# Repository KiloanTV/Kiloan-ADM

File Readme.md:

<div>
  <h1 align="center">Kiloan ADM V1</h1>

  <p align="center">
  <a href="https://blueprint.hackclub.com/">
    </img>
  </a>
  </p>
  <h1></h1>
  <p align="center">
    A 8-Channel Analog to Digital Converter for my custom digital mixing console!
  </p>
</div>

<sub align="center">This work is licensed under the
[MIT License](https://mit-license.org).
</sub>

## Table of Contents

- [About](#about)
- [Pictures](#pictures)
- [Bill of Materials](#bill-of-materials)

# About

I've always wanted my own digital mixing console, but those things are just too expensive for teenagers. That's why I want to build my own! This is the expansion board for 8 analog inputs, it receives power from the motherboard and outputs digital signals via the expansion connector to the Kiloan-APU board.

# Pictures

# Bill of Materials

<details>
<summary><strong>Show Bill Of Materials(BOM) ----></strong></summary>

|Designator                                                                                                        |Footprint                                  |Quantity|Value                               |LCSC Part #|
|------------------------------------------------------------------------------------------------------------------|-------------------------------------------|--------|------------------------------------|-----------|
|C1, C11, C12, C17, C18, C2, C25, C26, C29, C30, C39, C40, C45, C46, C51, C52, C59, C60, C7, C79, C8, C80, C83, C84|0805                                       |24      |100pF                               |C2167185   |
|C10, C19, C20, C27, C28, C3, C4, C41, C42, C49, C50, C75, C76, C81, C82, C9                                       |0805                                       |16      |220pF                               |C569853    |
|C13, C14, C15, C16, C21, C31, C32, C33, C34, C35, C37, C47, C55, C56, C57, C58, C85, C86, C87, C88                |CP_Radial_D5.0mm_P2.00mm                   |20      |100uF                               |C136287    |
|C22, C36, C38, C48, C53                                                                                           |0805                                       |5       |100nF                               |C3018562   |
|C23, C24, C43, C44, C5, C6, C77, C78                                                                              |0805                                       |8       |1nF                                 |C178423    |
|C54                                                                                                               |0805                                       |1       |4.7uF                               |C162418    |
|C61, C62, C63, C64, C65, C66, C67, C68, C71, C72, C74                                                             |0805                                       |11      |50V 100nF                           |C3018562   |
|C69, C70, C73                                                                                                     |0805                                       |3       |25V 10uF                            |C391262    |
|IC1                                                                                                               |QFN-64-1EP_9x9mm_P0.5mm_EP6x6mm_ThermalVias|1       |8-Channel Differential 32-bit △∑ ADC|C2655448   |
|IC201, IC202, IC203, IC204, IC205, IC206, IC207, IC208                                                            |SOIC-8_3.9x4.9mm_P1.27mm                   |8       |TI OPA1652AIDR                      |           |
|J1                                                                                                                |JST_PH_B4B-PH-K_1x04_P2.00mm_Vertical      |1       |PowerConAD-Wandler                  |C131334    |
|J2                                                                                                                |JST_PH_B8B-PH-K_1x08_P2.00mm_Vertical      |1       |AD-Wandler CON                      |C157974    |
|R1, R15, R16, R17, R18, R2, R32, R33, R36, R37, R52, R53, R54, R55, R68, R69                                      |0805                                       |16      |6800Ω                               |C2092414   |
|R10, R14, R21, R22, R27, R31, R41, R42, R47, R5, R51, R58, R59, R6, R63, R67                                      |0805                                       |16      |10Ω                                 |C2479122   |
|R11, R12, R24, R25, R28, R29, R44, R45, R48, R49, R60, R61, R64, R65, R7, R8                                      |0805                                       |16      |10kΩ                                |C2441435   |
|R13, R19, R20, R26, R3, R30, R39, R4, R40, R46, R50, R56, R57, R62, R66, R9                                       |0805                                       |16      |2200Ω                               |C2085959   |
|R23, R34, R35, R43                                                                                                |0805                                       |4       |20Ω                                 |C114557    |
|R38                                                                                                               |0805                                       |1       |33Ω ±1%                             |C126353    |
|X1                                                                                                                |JST_PHD_B26B-PHDSS_2x13_P2.00mm_Vertical   |1       |IN_CON                              |C3011993   |
| LCSC Quote: 47,54 Dollar + JLCPCP Quote: 27,65 Dollar                                                                                                                |    |        |                              |    |

</details>

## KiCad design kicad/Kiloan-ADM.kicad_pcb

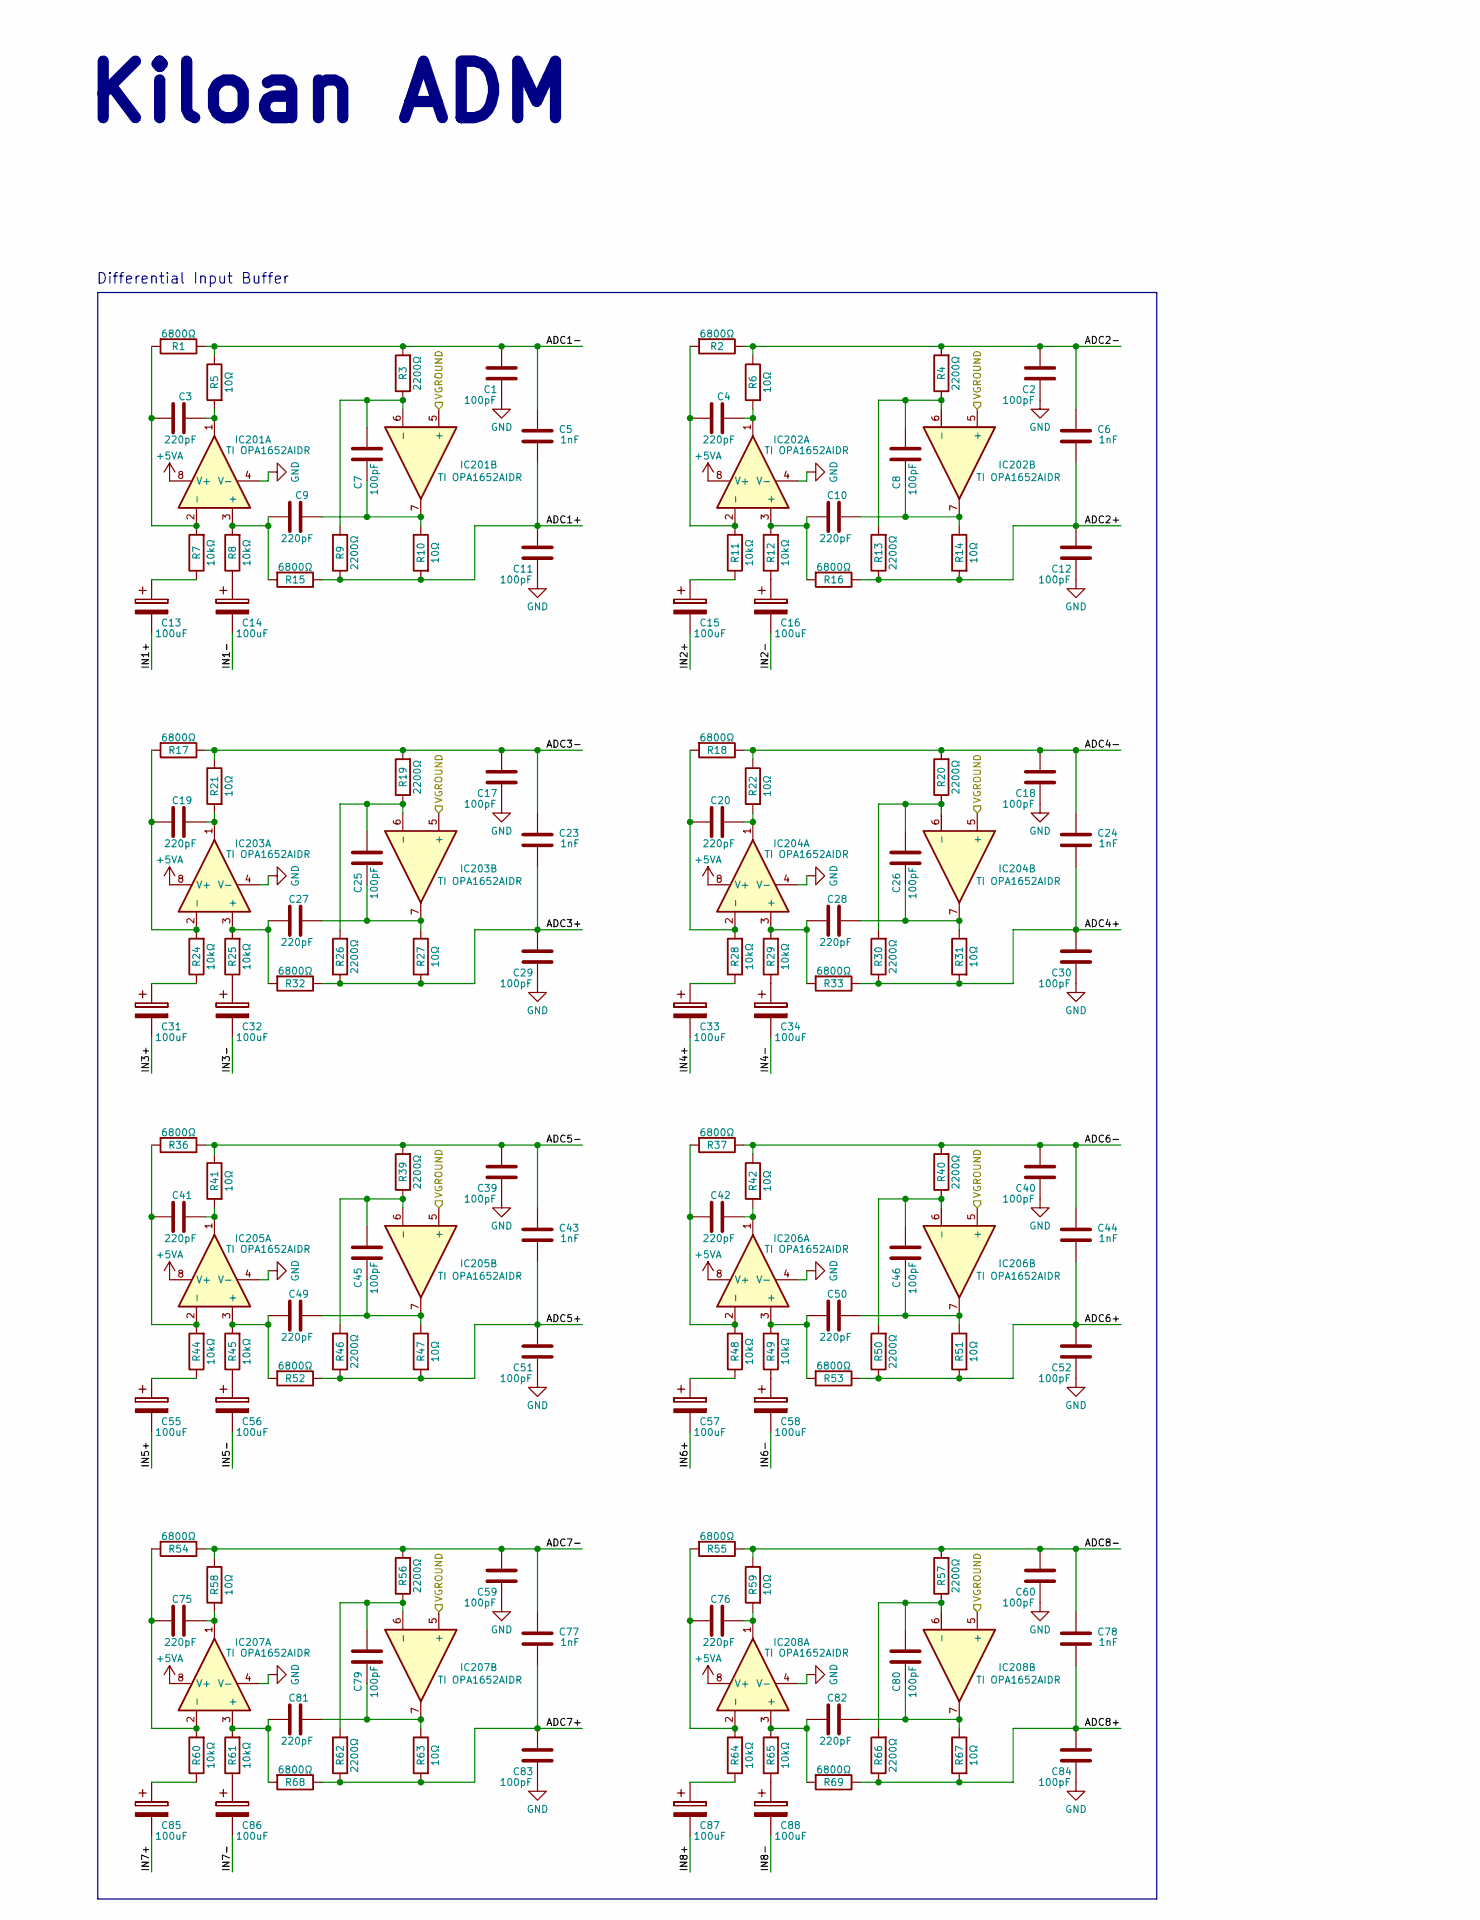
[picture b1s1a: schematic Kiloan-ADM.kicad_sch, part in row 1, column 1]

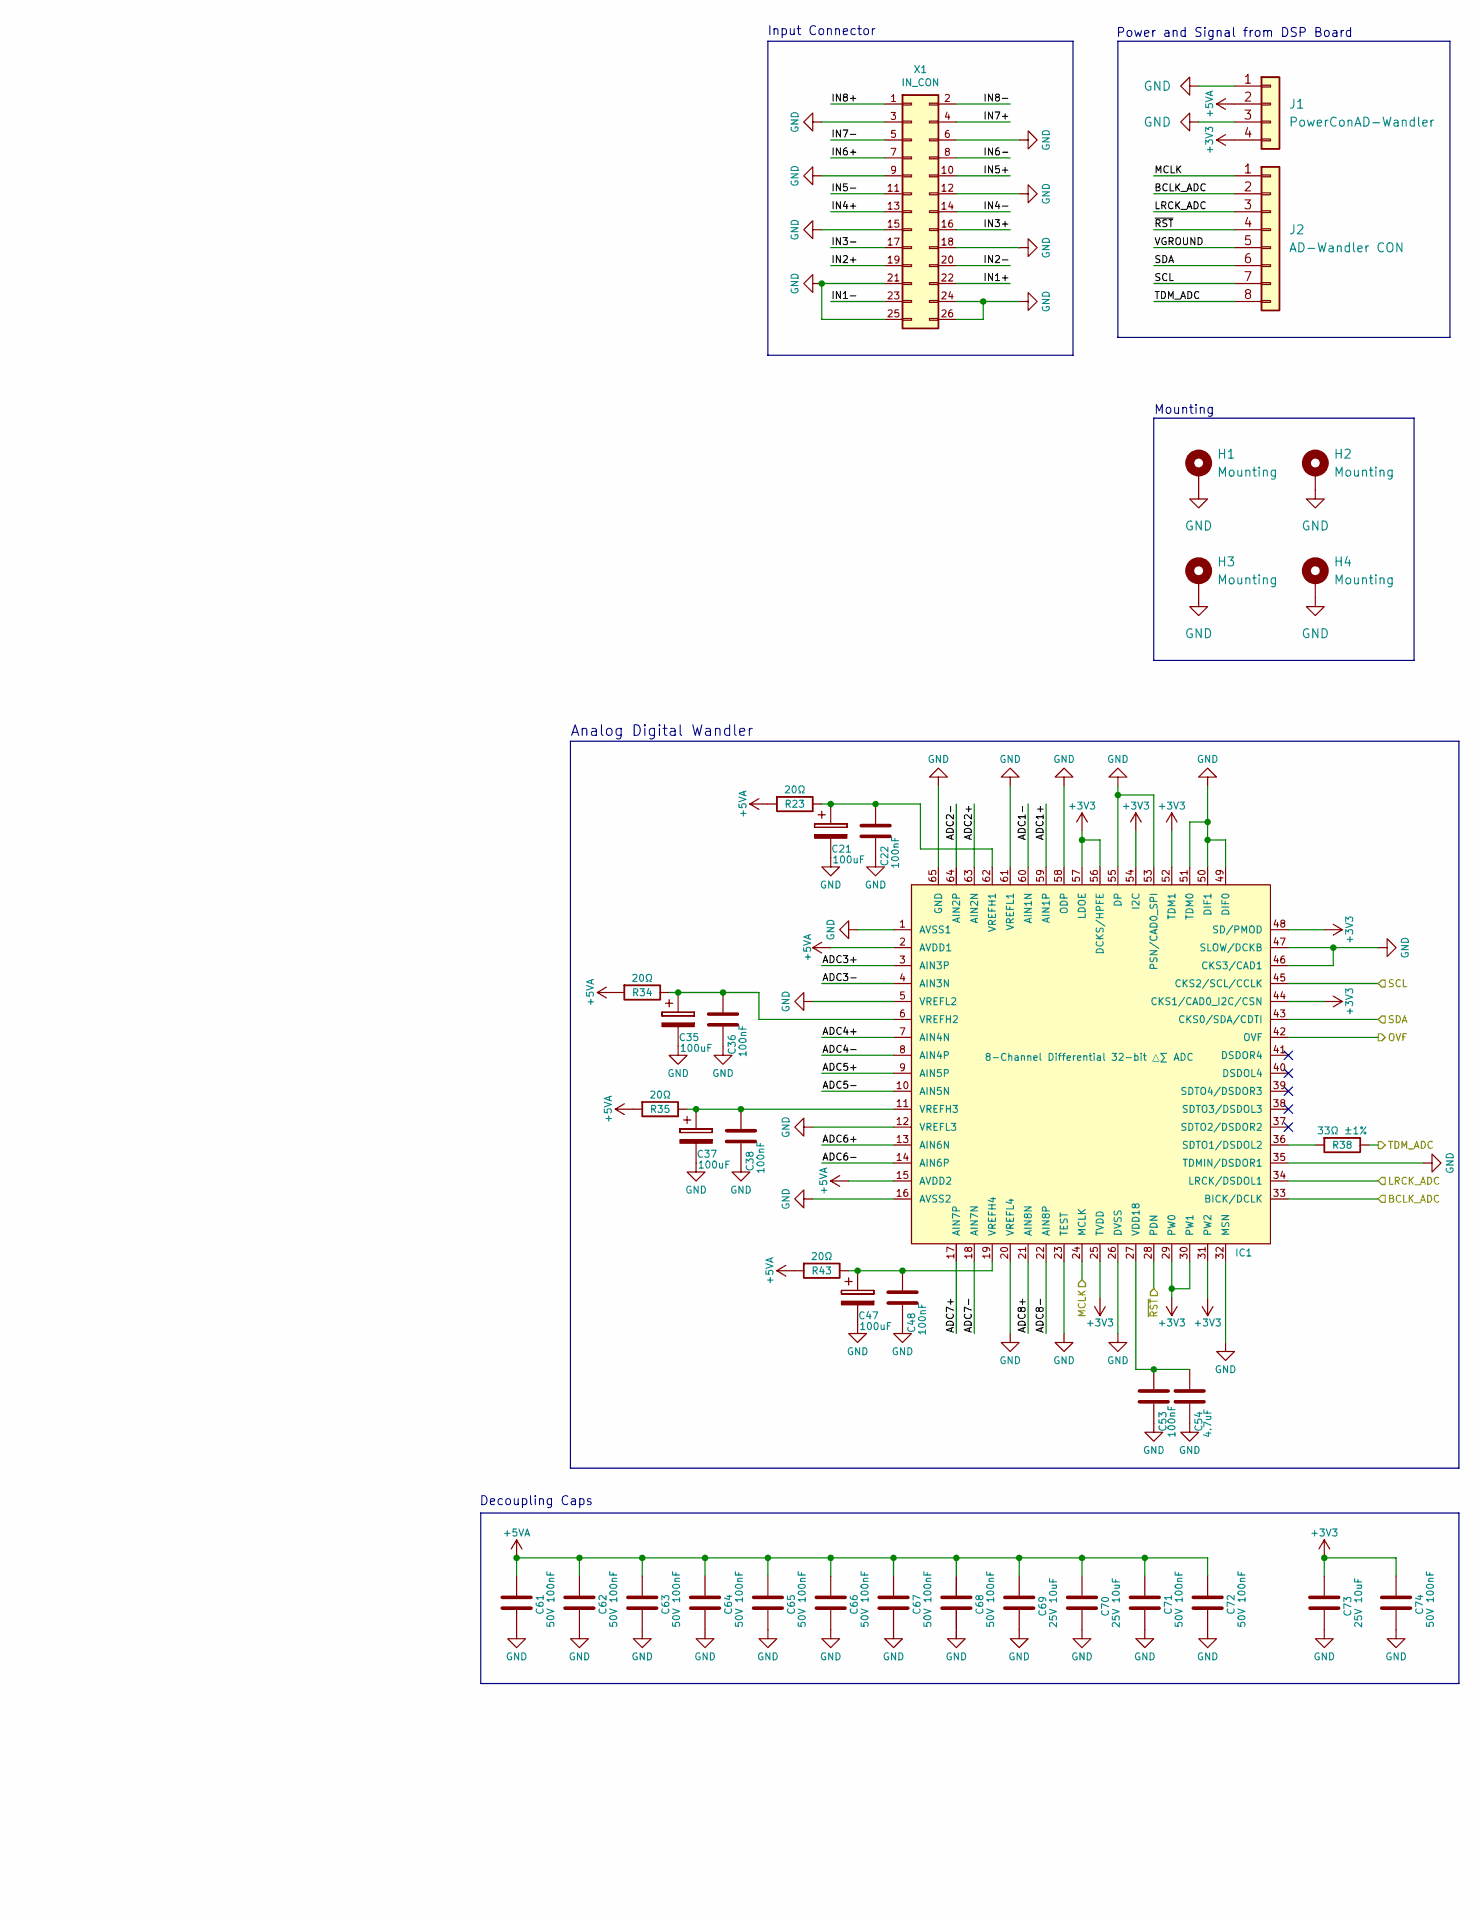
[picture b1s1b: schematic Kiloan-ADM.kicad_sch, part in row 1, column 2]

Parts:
C1, C2, C7, C8, C11, C12, C17, C18, C25, C26, C29, C30, C39, C40, C45, C46, C51, C52, C59, C60, C79, C80, C83, C84: 100pF; R_0805_2012Metric_Pad1.20x1.40mm_HandSolder; LCSC C2167185
C3, C4, C9, C10, C19, C20, C27, C28, C41, C42, C49, C50, C75, C76, C81, C82: 220pF; R_0805_2012Metric_Pad1.20x1.40mm_HandSolder; LCSC C569853
C5, C6, C23, C24, C43, C44, C77, C78: 1nF; R_0805_2012Metric_Pad1.20x1.40mm_HandSolder; LCSC C178423
C13, C14, C15, C16, C21, C31, C32, C33, C34, C35, C37, C47, C55, C56, C57, C58, C85, C86, C87, C88: 100uF; CP_Radial_D5.0mm_P2.00mm; LCSC C136287
C22, C36, C38, C48, C53: 100nF; C_0805_2012Metric_Pad1.18x1.45mm_HandSolder; LCSC C3018562
C54: 4.7uF; C_0805_2012Metric_Pad1.18x1.45mm_HandSolder; LCSC C162418
C61, C62, C63, C64, C65, C66, C67, C68, C71, C72, C74: 50V 100nF; C_0805_2012Metric_Pad1.18x1.45mm_HandSolder; LCSC C3018562
C69, C70, C73: 25V 10uF; C_0805_2012Metric_Pad1.18x1.45mm_HandSolder; LCSC C391262
H1, H2, H3, H4: Mounting; MountingHole_3.2mm_M3_Pad_Via
IC1: 8-Channel Differential 32-bit △∑ ADC; QFN-64-1EP_9x9mm_P0.5mm_EP6x6mm_ThermalVias; LCSC C2655448
IC201, IC202, IC203, IC204, IC205, IC206, IC207, IC208: TI OPA1652AIDR; SOIC-8_3.9x4.9mm_P1.27mm
J1: PowerConAD-Wandler; JST_PH_B4B-PH-K_1x04_P2.00mm_Vertical; LCSC C131334
J2: AD-Wandler CON; JST_PH_B8B-PH-K_1x08_P2.00mm_Vertical; LCSC C157974
R1, R2, R15, R16, R17, R18, R32, R33, R36, R37, R52, R53, R54, R55, R68, R69: 6800Ω; R_0805_2012Metric_Pad1.20x1.40mm_HandSolder; LCSC C2092414
R3, R4, R9, R13, R19, R20, R26, R30, R39, R40, R46, R50, R56, R57, R62, R66: 2200Ω; R_0805_2012Metric_Pad1.20x1.40mm_HandSolder; LCSC C2085959
R5, R6, R10, R14, R21, R22, R27, R31, R41, R42, R47, R51, R58, R59, R63, R67: 10Ω; R_0805_2012Metric_Pad1.20x1.40mm_HandSolder; LCSC C2479122
R7, R8, R11, R12, R24, R25, R28, R29, R44, R45, R48, R49, R60, R61, R64, R65: 10kΩ; R_0805_2012Metric_Pad1.20x1.40mm_HandSolder; LCSC C2441435
R23, R34, R35, R43: 20Ω; R_0805_2012Metric_Pad1.20x1.40mm_HandSolder; LCSC C114557
R38: 33Ω ±1%; R_0805_2012Metric_Pad1.20x1.40mm_HandSolder; LCSC C126353
X1: IN_CON; JST_PHD_B26B-PHDSS_2x13_P2.00mm_Vertical; LCSC C3011993

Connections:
+3V3: C73.1, C74.1, IC1.25 (TVDD), IC1.29 (PW0), IC1.30 (PW1), IC1.31 (PW2), IC1.44 (CKS1/CAD0_I2C/CSN), IC1.48 (SD/PMOD), IC1.52 (TDM1), IC1.54 (I2C), IC1.56 (DCKS/HPFE), IC1.57 (LDOE), J1.4 (3V3)
+5VA: C61.1, C62.1, C63.1, C64.1, C65.1, C66.1, C67.1, C68.1, C69.1, C70.1, C71.1, C72.1, IC1.2 (AVDD1), IC1.15 (AVDD2), IC201.8 (V+), IC202.8 (V+), IC203.8 (V+), IC204.8 (V+), IC205.8 (V+), IC206.8 (V+), IC207.8 (V+), IC208.8 (V+), J1.2 (5VA), R23.2, R34.2, R35.2, R43.2
/ADC1+: C5.2, C11.2, IC1.59 (AIN1P), R9.1, R10.2, R15.1
/ADC1-: C1.2, C5.1, IC1.60 (AIN1N), R1.1, R3.2, R5.1
/ADC2+: C6.2, C12.2, IC1.63 (AIN2N), R13.1, R14.2, R16.1
/ADC2-: C2.2, C6.1, IC1.64 (AIN2P), R2.1, R4.2, R6.1
/ADC3+: C23.2, C29.2, IC1.3 (AIN3P), R26.1, R27.2, R32.1
/ADC3-: C17.2, C23.1, IC1.4 (AIN3N), R17.1, R19.2, R21.1
/ADC4+: C24.2, C30.2, IC1.7 (AIN4N), R30.1, R31.2, R33.1
/ADC4-: C18.2, C24.1, IC1.8 (AIN4P), R18.1, R20.2, R22.1
/ADC5+: C43.2, C51.2, IC1.9 (AIN5P), R46.1, R47.2, R52.1
/ADC5-: C39.2, C43.1, IC1.10 (AIN5N), R36.1, R39.2, R41.1
/ADC6+: C44.2, C52.2, IC1.13 (AIN6N), R50.1, R51.2, R53.1
/ADC6-: C40.2, C44.1, IC1.14 (AIN6P), R37.1, R40.2, R42.1
/ADC7+: C77.2, C83.2, IC1.17 (AIN7P), R62.1, R63.2, R68.1
/ADC7-: C59.2, C77.1, IC1.18 (AIN7N), R54.1, R56.2, R58.1
/ADC8+: C78.2, C84.2, IC1.21 (AIN8N), R66.1, R67.2, R69.1
/ADC8-: C60.2, C78.1, IC1.22 (AIN8P), R55.1, R57.2, R59.1
/BCLK_ADC: IC1.33 (BICK/DCLK), J2.2 (BCLK)
/IN1+: C13.2, X1.22
/IN1-: C14.2, X1.23
/IN2+: C15.2, X1.19
/IN2-: C16.2, X1.20
/IN3+: C31.2, X1.16
/IN3-: C32.2, X1.17
/IN4+: C33.2, X1.13
/IN4-: C34.2, X1.14
/IN5+: C55.2, X1.10
/IN5-: C56.2, X1.11
/IN6+: C57.2, X1.7
/IN6-: C58.2, X1.8
/IN7+: C85.2, X1.4
/IN7-: C86.2, X1.5
/IN8+: C87.2, X1.1
/IN8-: C88.2, X1.2
/LRCK_ADC: IC1.34 (LRCK/DSDOL1), J2.3 (LRCK)
/MCLK: IC1.24 (MCLK), J2.1 (MCLK)
/OVF: IC1.42 (OVF)
/SCL: IC1.45 (CKS2/SCL/CCLK), J2.7 (SCL)
/SDA: IC1.43 (CKS0/SDA/CDTI), J2.6 (SDA)
/TDM_ADC: J2.8 (TDM), R38.1
/VGROUND: IC201.5 (+), IC202.5 (+), IC203.5 (+), IC204.5 (+), IC205.5 (+), IC206.5 (+), IC207.5 (+), IC208.5 (+), J2.5 (VGROUND)
/~RST: IC1.28 (PDN), J2.4 (RST)
GND: C1.1, C2.1, C11.1, C12.1, C17.1, C18.1, C21.2, C22.2, C29.1, C30.1, C35.2, C36.2, C37.2, C38.2, C39.1, C40.1, C47.2, C48.2, C51.1, C52.1, C53.2, C54.2, C59.1, C60.1, C61.2, C62.2, C63.2, C64.2, C65.2, C66.2, C67.2, C68.2, C69.2, C70.2, C71.2, C72.2, C73.2, C74.2, C83.1, C84.1, H1.1, H2.1, H3.1, H4.1, IC1.1 (AVSS1), IC1.5 (VREFL2), IC1.12 (VREFL3), IC1.16 (AVSS2), IC1.20 (VREFL4), IC1.23 (TEST), IC1.26 (DVSS), IC1.32 (MSN), IC1.35 (TDMIN/DSDOR1), IC1.46 (CKS3/CAD1), IC1.47 (SLOW/DCKB), IC1.49 (DIF0), IC1.50 (DIF1), IC1.51 (TDM0), IC1.53 (PSN/CAD0_SPI), IC1.55 (DP), IC1.58 (ODP), IC1.61 (VREFL1), IC1.65 (GND), IC201.4 (V-), IC202.4 (V-), IC203.4 (V-), IC204.4 (V-), IC205.4 (V-), IC206.4 (V-), IC207.4 (V-), IC208.4 (V-), J1.1 (GND), J1.3 (GND), X1.3, X1.6, X1.9, X1.12, X1.15, X1.18, X1.21, X1.24, X1.25, X1.26
unnamed: C3.2, IC201.1, R5.2
unnamed: C4.2, IC202.1, R6.2
unnamed: C7.1, C9.2, IC201.7, R10.1
unnamed: C8.1, C10.2, IC202.7, R14.1
unnamed: C13.1, R7.1
unnamed: C14.1, R8.1
unnamed: C15.1, R11.1
unnamed: C16.1, R12.1
unnamed: C19.2, IC203.1, R21.2
unnamed: C20.2, IC204.1, R22.2
unnamed: C25.1, C27.2, IC203.7, R27.1
unnamed: C26.1, C28.2, IC204.7, R31.1
unnamed: C31.1, R24.1
unnamed: C32.1, R25.1
unnamed: C33.1, R28.1
unnamed: C34.1, R29.1
unnamed: C41.2, IC205.1, R41.2
unnamed: C42.2, IC206.1, R42.2
unnamed: C45.1, C49.2, IC205.7, R47.1
unnamed: C46.1, C50.2, IC206.7, R51.1
unnamed: C55.1, R44.1
unnamed: C56.1, R45.1
unnamed: C57.1, R48.1
unnamed: C58.1, R49.1
unnamed: C75.2, IC207.1, R58.2
unnamed: C76.2, IC208.1, R59.2
unnamed: C79.1, C81.2, IC207.7, R63.1
unnamed: C80.1, C82.2, IC208.7, R67.1
unnamed: C85.1, R60.1
unnamed: C86.1, R61.1
unnamed: C87.1, R64.1
unnamed: C88.1, R65.1
unnamed: IC1.36 (SDTO1/DSDOL2), R38.2
unnamed: C53.1, C54.1, IC1.27 (VDD18)
unnamed: C21.1, C22.1, IC1.62 (VREFH1), R23.1
unnamed: C35.1, C36.1, IC1.6 (VREFH2), R34.1
unnamed: C37.1, C38.1, IC1.11 (VREFH3), R35.1
unnamed: C47.1, C48.1, IC1.19 (VREFH4), R43.1
unnamed: C9.1, IC201.3 (+), R8.2, R15.2
unnamed: C3.1, IC201.2 (-), R1.2, R7.2
unnamed: C7.2, IC201.6 (-), R3.1, R9.2
unnamed: C10.1, IC202.3 (+), R12.2, R16.2
unnamed: C4.1, IC202.2 (-), R2.2, R11.2
unnamed: C8.2, IC202.6 (-), R4.1, R13.2
unnamed: C27.1, IC203.3 (+), R25.2, R32.2
unnamed: C19.1, IC203.2 (-), R17.2, R24.2
unnamed: C25.2, IC203.6 (-), R19.1, R26.2
unnamed: C28.1, IC204.3 (+), R29.2, R33.2
unnamed: C20.1, IC204.2 (-), R18.2, R28.2
unnamed: C26.2, IC204.6 (-), R20.1, R30.2
unnamed: C49.1, IC205.3 (+), R45.2, R52.2
unnamed: C41.1, IC205.2 (-), R36.2, R44.2
unnamed: C45.2, IC205.6 (-), R39.1, R46.2
unnamed: C50.1, IC206.3 (+), R49.2, R53.2
unnamed: C42.1, IC206.2 (-), R37.2, R48.2
unnamed: C46.2, IC206.6 (-), R40.1, R50.2
unnamed: C81.1, IC207.3 (+), R61.2, R68.2
unnamed: C75.1, IC207.2 (-), R54.2, R60.2
unnamed: C79.2, IC207.6 (-), R56.1, R62.2
unnamed: C82.1, IC208.3 (+), R65.2, R69.2
unnamed: C76.1, IC208.2 (-), R55.2, R64.2
unnamed: C80.2, IC208.6 (-), R57.1, R66.2

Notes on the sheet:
Mounting
Analog Digital Wandler
Kiloan ADM
Input Connector
Power and Signal from DSP Board
Differential Input Buffer
Decoupling Caps

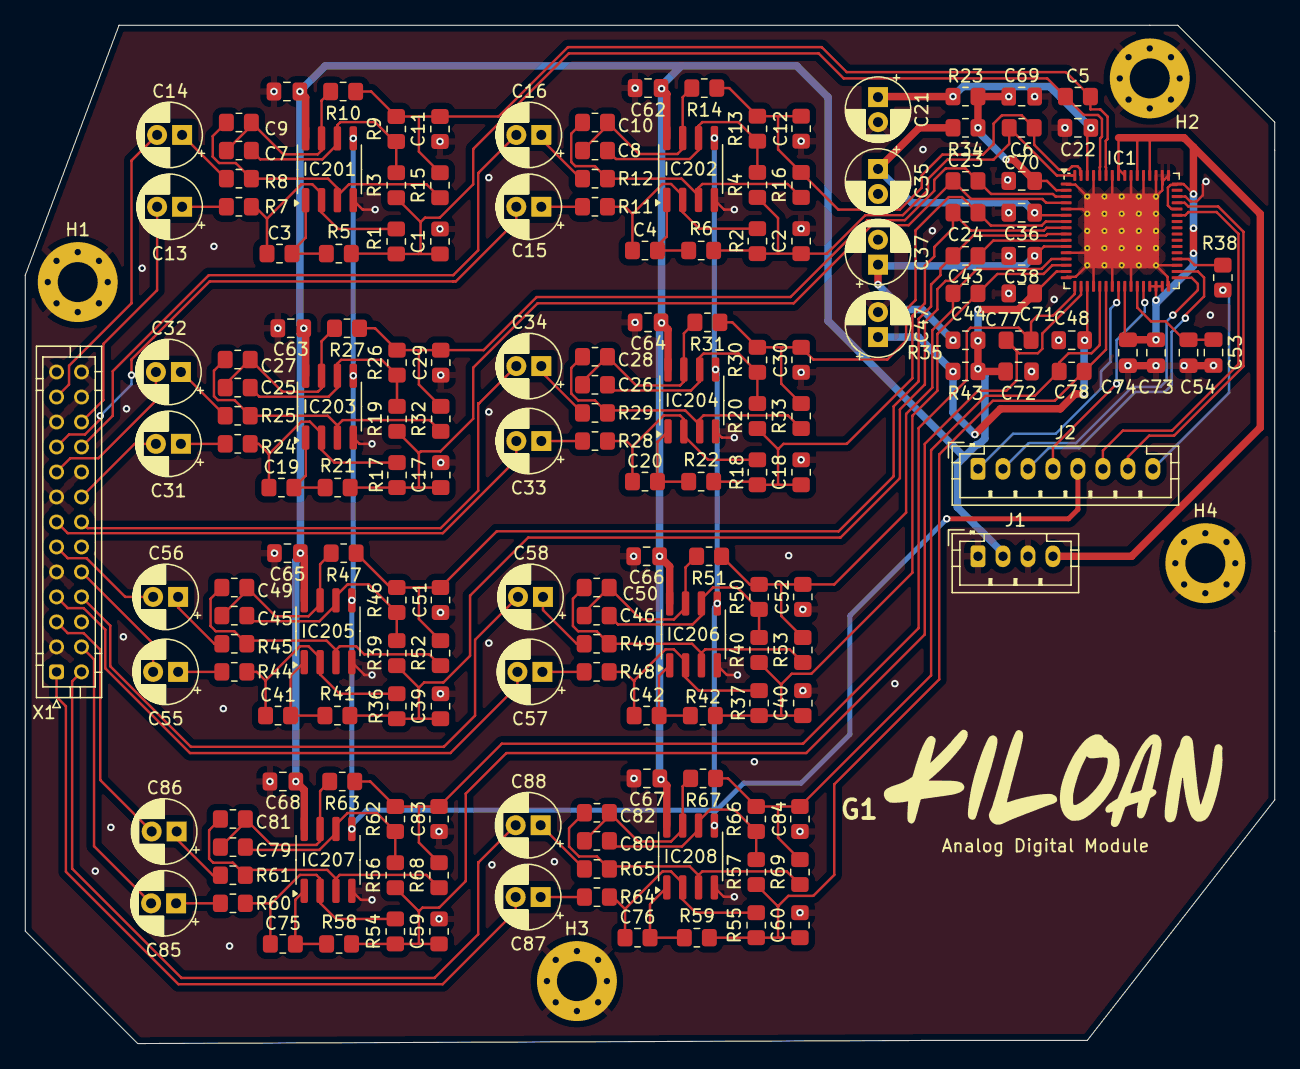
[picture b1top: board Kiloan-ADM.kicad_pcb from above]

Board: 2 copper layers, 100.0 x 81.5 mm, 174 parts (0 on the bottom side), 105 nets.

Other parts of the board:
G1: LOGO

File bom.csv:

Designator,Footprint,Quantity,Value,LCSC Part #
"C1, C11, C12, C17, C18, C2, C25, C26, C29, C30, C39, C40, C45, C46, C51, C52, C59, C60, C7, C79, C8, C80, C83, C84",0805,24,100pF,C2167185
"C10, C19, C20, C27, C28, C3, C4, C41, C42, C49, C50, C75, C76, C81, C82, C9",0805,16,220pF,C569853
"C13, C14, C15, C16, C21, C31, C32, C33, C34, C35, C37, C47, C55, C56, C57, C58, C85, C86, C87, C88",CP_Radial_D5.0mm_P2.00mm,20,100uF,C136287
"C22, C36, C38, C48, C53",0805,5,100nF,C3018562
"C23, C24, C43, C44, C5, C6, C77, C78",0805,8,1nF,C178423
C54,0805,1,4.7uF,C162418
"C61, C62, C63, C64, C65, C66, C67, C68, C71, C72, C74",0805,11,50V 100nF,C3018562
"C69, C70, C73",0805,3,25V 10uF,C391262
IC1,QFN-64-1EP_9x9mm_P0.5mm_EP6x6mm_ThermalVias,1,8-Channel Differential 32-bit △∑ ADC,C2655448
"IC201, IC202, IC203, IC204, IC205, IC206, IC207, IC208",SOIC-8_3.9x4.9mm_P1.27mm,8,TI OPA1652AIDR,
J1,JST_PH_B4B-PH-K_1x04_P2.00mm_Vertical,1,PowerConAD-Wandler,C131334
J2,JST_PH_B8B-PH-K_1x08_P2.00mm_Vertical,1,AD-Wandler CON,C157974
"R1, R15, R16, R17, R18, R2, R32, R33, R36, R37, R52, R53, R54, R55, R68, R69",0805,16,6800Ω,C2092414
"R10, R14, R21, R22, R27, R31, R41, R42, R47, R5, R51, R58, R59, R6, R63, R67",0805,16,10Ω,C2479122
"R11, R12, R24, R25, R28, R29, R44, R45, R48, R49, R60, R61, R64, R65, R7, R8",0805,16,10kΩ,C2441435
"R13, R19, R20, R26, R3, R30, R39, R4, R40, R46, R50, R56, R57, R62, R66, R9",0805,16,2200Ω,C2085959
"R23, R34, R35, R43",0805,4,20Ω,C114557
R38,0805,1,33Ω ±1%,C126353
X1,JST_PHD_B26B-PHDSS_2x13_P2.00mm_Vertical,1,IN_CON,C3011993

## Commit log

2025-11-20 add finished project for blueprint
    _ Kian
